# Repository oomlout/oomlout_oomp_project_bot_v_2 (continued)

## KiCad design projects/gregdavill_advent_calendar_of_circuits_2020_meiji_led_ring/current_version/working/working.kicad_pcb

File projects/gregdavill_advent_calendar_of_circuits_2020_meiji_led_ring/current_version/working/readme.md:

# advent_calendar_of_circuits_2020
 
## summary 
* id: gregdavill_advent_calendar_of_circuits_2020_meiji_led_ring
* user: gregdavill
* name: advent_calendar_of_circuits_2020
* board: meiji_led_ring
* repo: https://github.com/gregdavill/advent-calendar-of-circuits-2020
* src_file_repo_kicad_pcb: meiji-led-ring/kicad-src/meiji-led-ring.kicad_pcb
* src_file_repo_kicad_pcb_link: https://github.com/gregdavill/advent-calendar-of-circuits-2020/tree/main/meiji-led-ring/kicad-src/meiji-led-ring.kicad_pcb
* src_file_repo_kicad_sch: meiji-led-ring/kicad-src/meiji-led-ring.kicad_sch
* src_file_repo_kicad_sch_link: https://github.com/gregdavill/advent-calendar-of-circuits-2020/tree/main/meiji-led-ring/kicad-src/meiji-led-ring.kicad_sch

* src_file_repo_sch: 
* src_file_repo_sch_link: https://github.com/gregdavill/advent-calendar-of-circuits-2020/tree/main/
* full details link: https://github.com/oomlout/oomlout_oomp_project_bot_v_2/tree/main/projects/gregdavill_advent_calendar_of_circuits_2020_meiji_led_ring/current_version/working

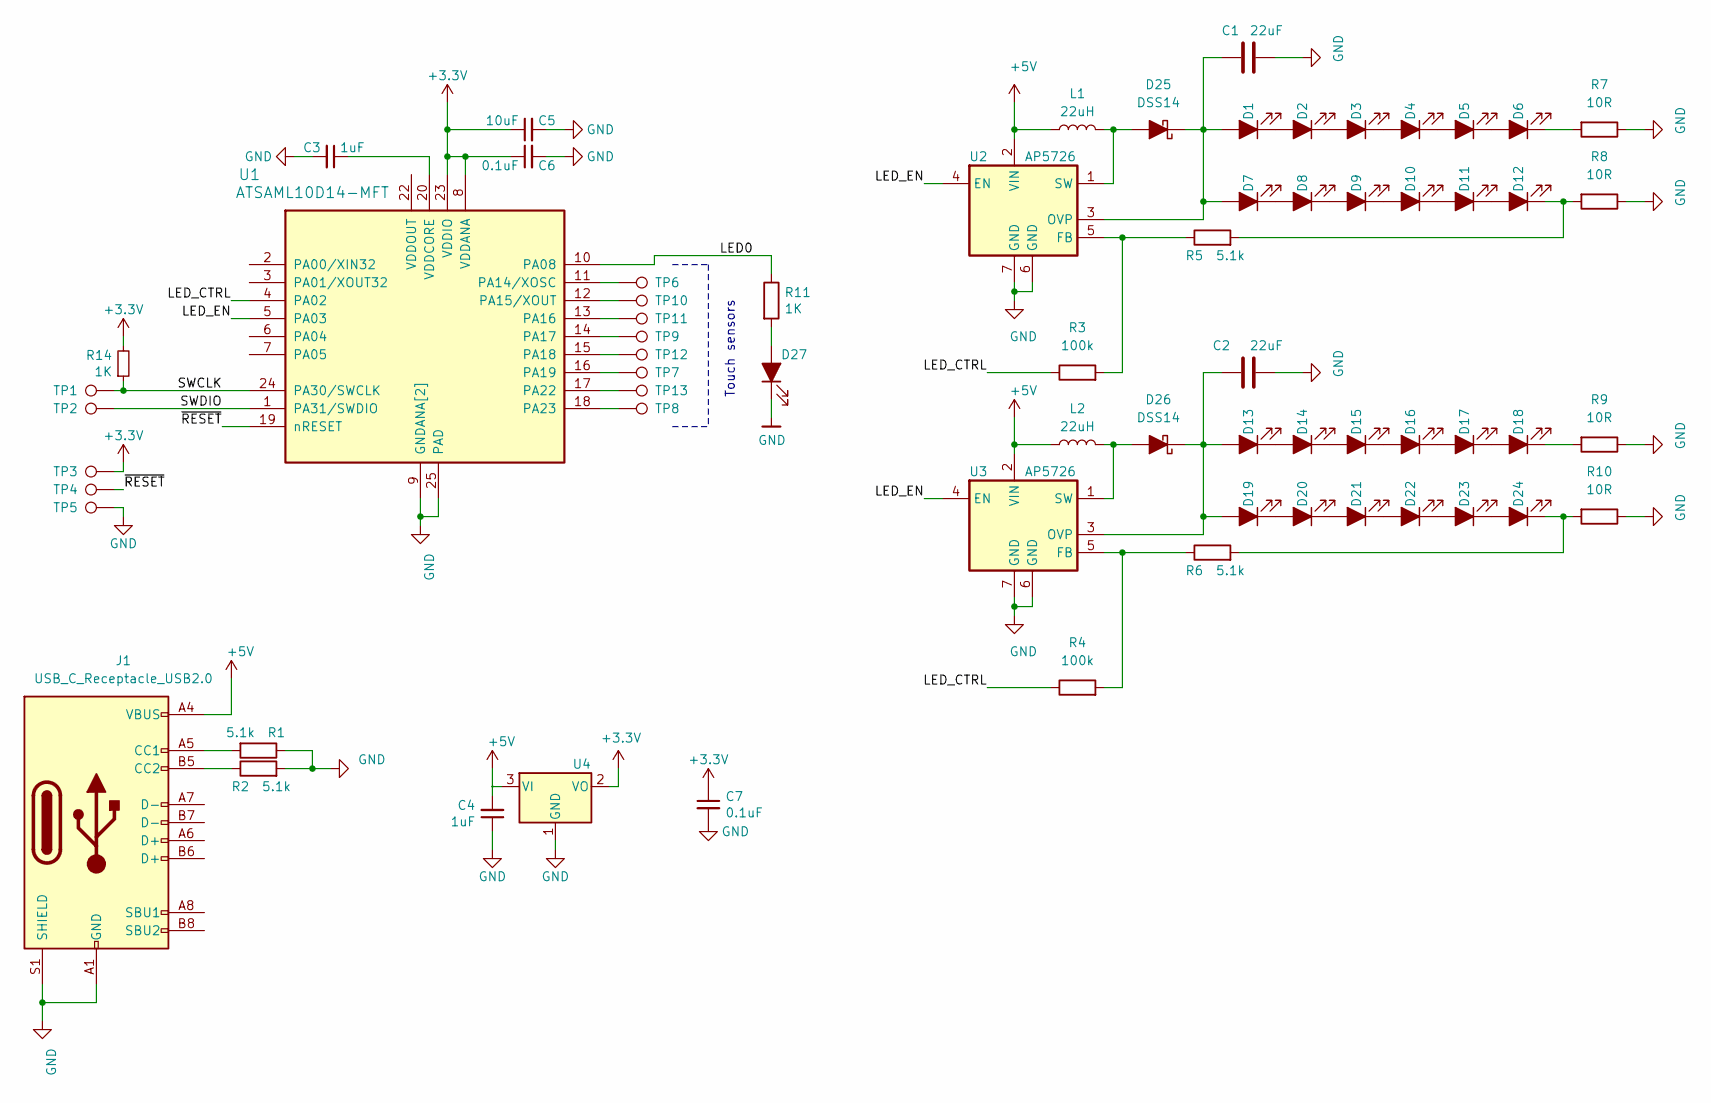
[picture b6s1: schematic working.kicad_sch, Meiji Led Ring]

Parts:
C1, C2: 22uF; C_1210_3225Metric
C3, C4: 1uF; C_0402_1005Metric
C5: 10uF; C_0402_1005Metric
C6, C7: 0.1uF; C_0402_1005Metric
D1, D2, D3, D4, D5, D6, D7, D8, D9, D10, D11, D12, D13, D14, D15, D16, D17, D18, D19, D20, D21, D22, D23, D24: LED_ALT; LED_LUXEON_3014
D25, D26: DSS14; D_SOD-123F
D27: LED_ALT; LED_0402_1005Metric
J1: USB_C_Receptacle_USB2.0; USB_C_Receptacle_HRO_TYPE-C-31-M-12
L1, L2: 22uH; L_Taiyo-Yuden_NR-40xx
R1, R2, R5, R6: 5.1k; R_0402_1005Metric
R3, R4: 100k; R_0402_1005Metric
R7, R8, R9, R10: 10R; R_0603_1608Metric
R11, R14: 1K; R_0402_1005Metric
TP1: TP_SWCLK; TestPoint_Pad_D1.0mm
TP2: TP_SWDIO; TestPoint_Pad_D1.0mm
TP3: TP_VDD; TestPoint_Pad_D1.0mm
TP4: TP_RESET; TestPoint_Pad_D1.0mm
TP5: TP_GND; TestPoint_Pad_D1.0mm
TP6, TP7, TP8, TP9, TP10, TP11, TP12, TP13: TP_SWCLK; touch_edge_arc
U1: ATSAML10D14-MFT; QFN-24-1EP_5x5mm_P0.65mm_EP3.4x3.4mm
U2, U3: AP5726; DFN-6-1EP_2x2mm_P0.65mm_EP1x1.6mm
U4: MCP1700-3302E_SOT23; SOT-23

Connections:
+3V3: C5.1, C6.1, C7.1, R14.2, TP3.1, U1.8 (VDDANA), U1.23 (VDDIO), U4.2 (VO)
+5V: C4.2, J1.A4 (VBUS), J1.A9 (VBUS), J1.B4 (VBUS), J1.B9 (VBUS), L1.1, L2.1, U2.2 (VIN), U3.2 (VIN), U4.3 (VI)
/LED0: R11.1, U1.10 (PA08)
/LED_CTRL: R3.1, R4.1, U1.4 (PA02)
/LED_EN: U1.5 (PA03), U2.4 (EN), U3.4 (EN)
/SWCLK: R14.1, TP1.1, U1.24 (PA30/SWCLK)
/SWDIO: TP2.1, U1.1 (PA31/SWDIO)
/~RESET: TP4.1, U1.19 (nRESET)
GND: C1.2, C2.2, C3.2, C4.1, C5.2, C6.2, C7.2, D27.1 (K), J1.A1 (GND), J1.A12 (GND), J1.B1 (GND), J1.B12 (GND), J1.S1 (SHIELD), R1.1, R2.2, R7.1, R8.1, R9.1, R10.1, TP5.1, U1.9 (GNDANA[2]), U1.21 (GNDANA[2]), U1.25 (PAD), U2.6 (GND), U2.7 (GND), U3.6 (GND), U3.7 (GND), U4.1 (GND)
unnamed: C1.1, D1.2 (A), D7.2 (A), D25.1 (K), U2.3 (OVP)
unnamed: C2.1, D13.2 (A), D19.2 (A), D26.1 (K), U3.3 (OVP)
unnamed: C3.1, U1.20 (VDDCORE)
unnamed: D1.1 (K), D2.2 (A)
unnamed: D2.1 (K), D3.2 (A)
unnamed: D3.1 (K), D4.2 (A)
unnamed: D4.1 (K), D5.2 (A)
unnamed: D5.1 (K), D6.2 (A)
unnamed: D6.1 (K), R7.2
unnamed: D7.1 (K), D8.2 (A)
unnamed: D8.1 (K), D9.2 (A)
unnamed: D10.1 (K), D11.2 (A)
unnamed: D9.1 (K), D10.2 (A)
unnamed: D11.1 (K), D12.2 (A)
unnamed: D12.1 (K), R5.2, R8.2
unnamed: D13.1 (K), D14.2 (A)
unnamed: D14.1 (K), D15.2 (A)
unnamed: D15.1 (K), D16.2 (A)
unnamed: D16.1 (K), D17.2 (A)
unnamed: D17.1 (K), D18.2 (A)
unnamed: D18.1 (K), R9.2
unnamed: D19.1 (K), D20.2 (A)
unnamed: D20.1 (K), D21.2 (A)
unnamed: D21.1 (K), D22.2 (A)
unnamed: D22.1 (K), D23.2 (A)
unnamed: D23.1 (K), D24.2 (A)
unnamed: D24.1 (K), R6.2, R10.2
unnamed: D25.2 (A), L1.2, U2.1 (SW)
unnamed: D26.2 (A), L2.2, U3.1 (SW)
unnamed: D27.2 (A), R11.2
unnamed: J1.A5 (CC1), R1.2
unnamed: J1.B5 (CC2), R2.1
unnamed: R3.2, R5.1, U2.5 (FB)
unnamed: R4.2, R6.1, U3.5 (FB)
unnamed: TP6.1, U1.11 (PA14/XOSC)
unnamed: TP7.1, U1.16 (PA19)
unnamed: TP8.1, U1.18 (PA23)
unnamed: TP9.1, U1.14 (PA17)
unnamed: TP10.1, U1.12 (PA15/XOUT)
unnamed: TP11.1, U1.13 (PA16)
unnamed: TP12.1, U1.15 (PA18)
unnamed: TP13.1, U1.17 (PA22)

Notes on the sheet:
Touch sensors

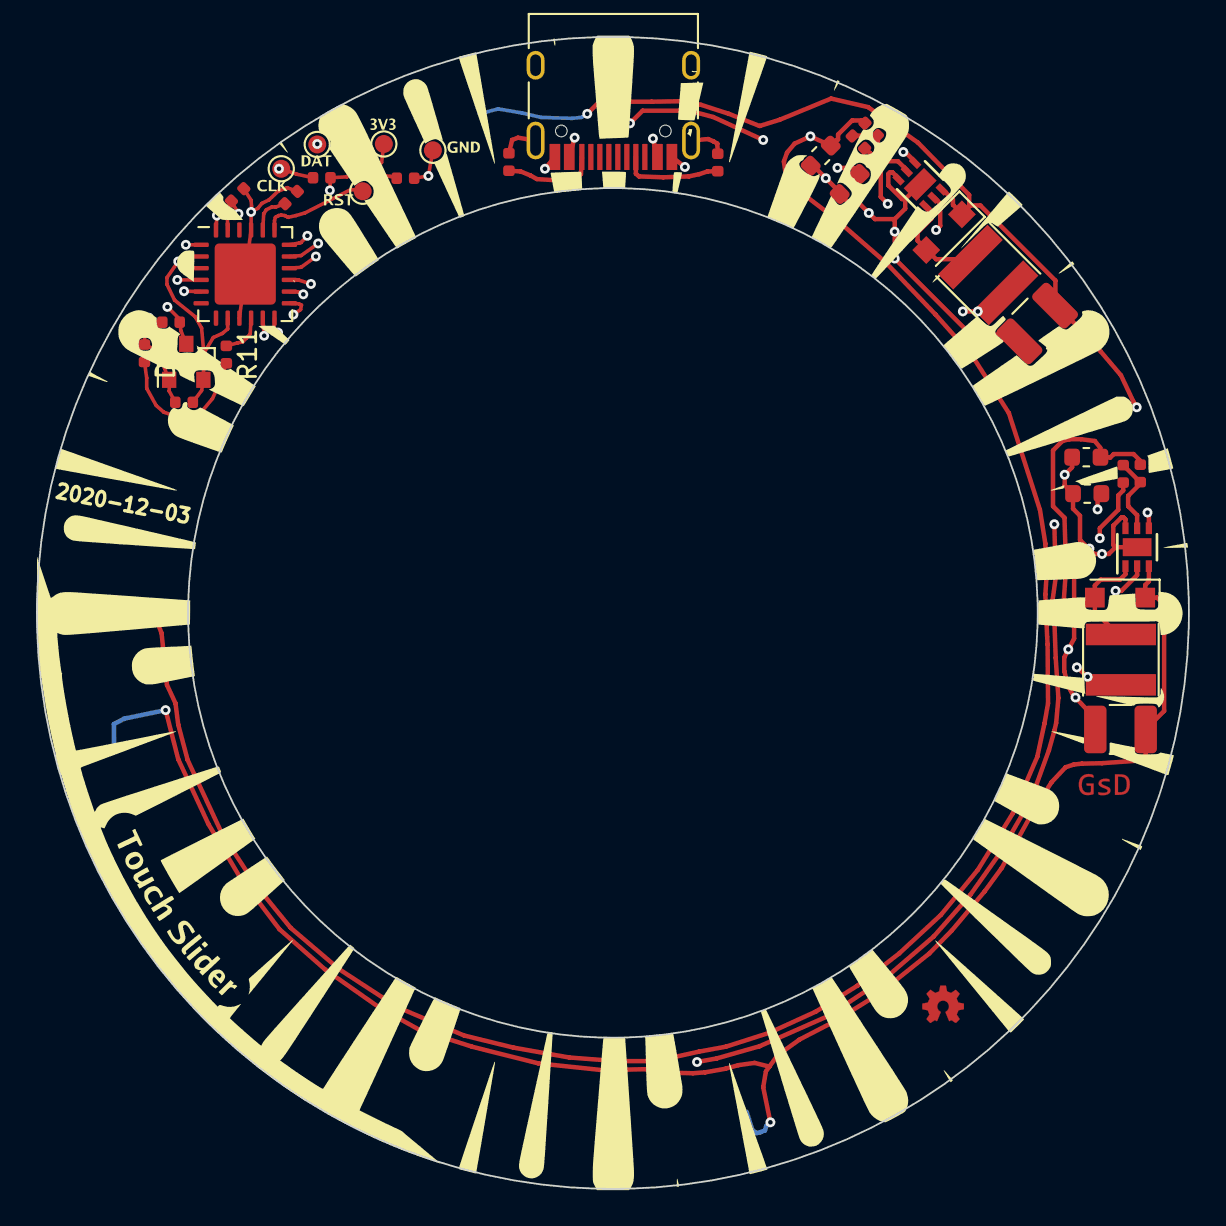
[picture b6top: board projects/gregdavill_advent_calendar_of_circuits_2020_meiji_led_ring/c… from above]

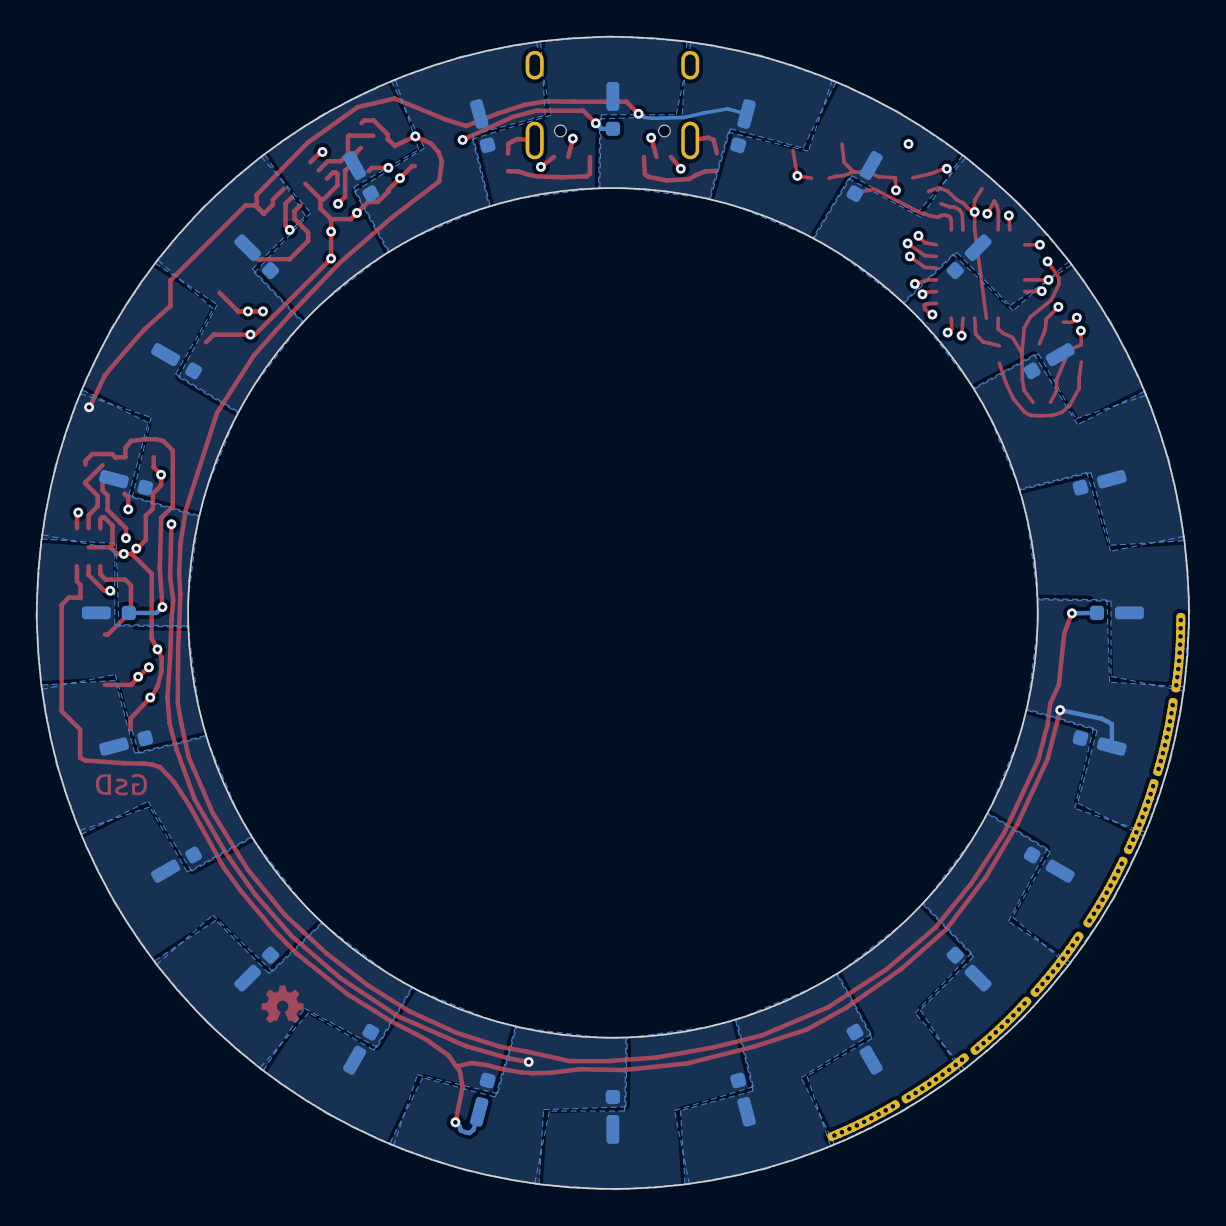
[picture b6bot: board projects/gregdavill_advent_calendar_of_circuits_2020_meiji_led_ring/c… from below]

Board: 4 copper layers, 64.0 x 64.0 mm, 66 parts (24 on the bottom side), 51 nets.

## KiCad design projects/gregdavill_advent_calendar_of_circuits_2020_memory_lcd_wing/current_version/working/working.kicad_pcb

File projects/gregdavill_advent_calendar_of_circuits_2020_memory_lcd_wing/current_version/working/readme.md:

# advent_calendar_of_circuits_2020
 
## summary 
* id: gregdavill_advent_calendar_of_circuits_2020_memory_lcd_wing
* user: gregdavill
* name: advent_calendar_of_circuits_2020
* board: memory_lcd_wing
* repo: https://github.com/gregdavill/advent-calendar-of-circuits-2020
* src_file_repo_kicad_pcb: memory-lcd-wing/kicad-src/memory-lcd-wing.kicad_pcb
* src_file_repo_kicad_pcb_link: https://github.com/gregdavill/advent-calendar-of-circuits-2020/tree/main/memory-lcd-wing/kicad-src/memory-lcd-wing.kicad_pcb
* src_file_repo_kicad_sch: memory-lcd-wing/kicad-src/memory-lcd-wing.kicad_sch
* src_file_repo_kicad_sch_link: https://github.com/gregdavill/advent-calendar-of-circuits-2020/tree/main/memory-lcd-wing/kicad-src/memory-lcd-wing.kicad_sch

* src_file_repo_sch: 
* src_file_repo_sch_link: https://github.com/gregdavill/advent-calendar-of-circuits-2020/tree/main/
* full details link: https://github.com/oomlout/oomlout_oomp_project_bot_v_2/tree/main/projects/gregdavill_advent_calendar_of_circuits_2020_memory_lcd_wing/current_version/working

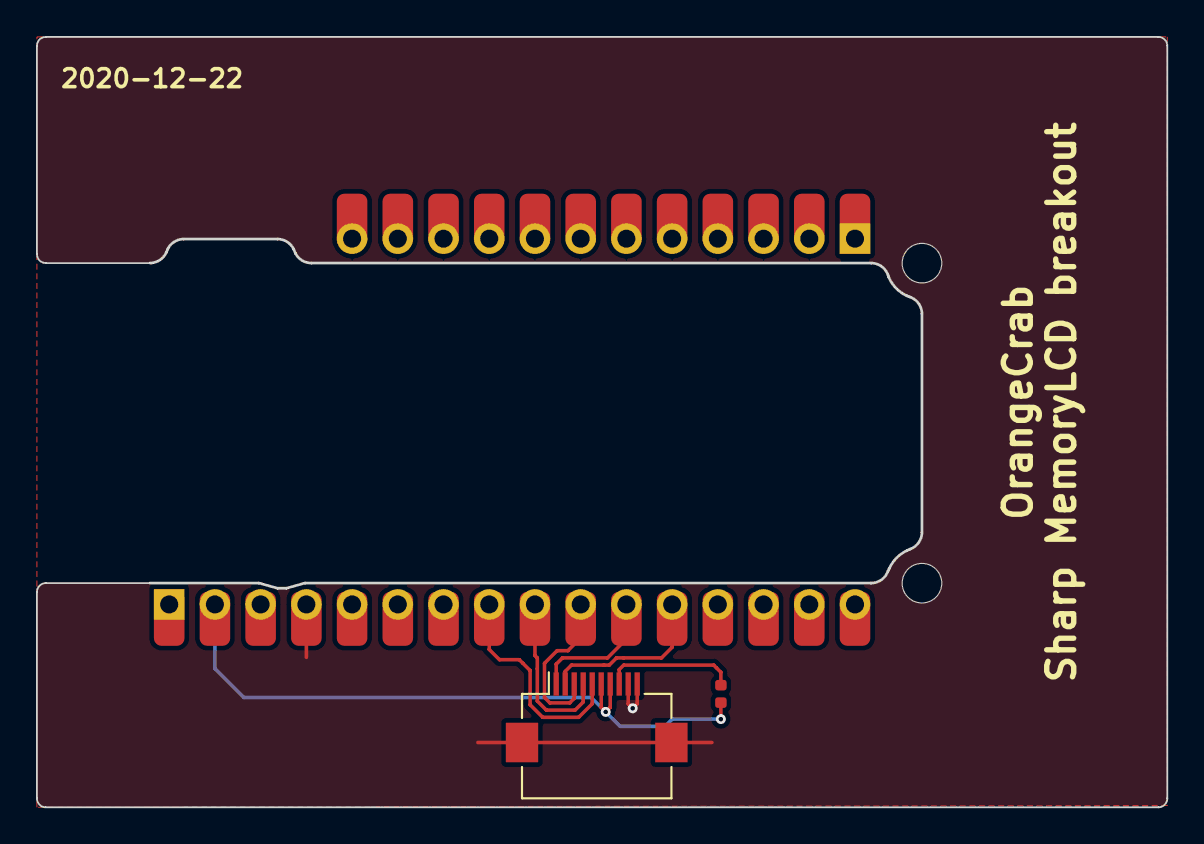
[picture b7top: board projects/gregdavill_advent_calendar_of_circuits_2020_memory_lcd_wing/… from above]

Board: 2 copper layers, 62.8 x 42.8 mm, 4 parts (0 on the bottom side), 8 nets.

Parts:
J1: Conn_01x16; PinHeader_1x16_P2.54mm_Vertical
J2: Conn_01x12; PinHeader_1x12_P2.54mm_Vertical
J3: Conn_01x10_MountingPin; Hirose_FH12-10S-0.5SH_1x10-1MP_P0.50mm_Horizontal
R1: 0R; R_0402_1005Metric

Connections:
+3V3: J1.2, J3.6, J3.7, R1.1
/DISP: J1.8, J3.5
/EXTCOMIN: J1.9, J3.4
/EXTMODE: J3.8, R1.2
/SCS: J1.10, J3.3
/mo: J1.12, J3.2
/sck: J1.11, J3.1
GND: J1.4, J3.9, J3.10, J3.MP (MountPin)
